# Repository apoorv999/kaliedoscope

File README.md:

# Kaliedoscope
This project is arduino based Kaliedoscope, developed at CEDT, NSUT. It comprises of two layers of boards. Top layer contains 4 RGB LEDs, switch, USB port for charging and connector for lipo battery. The  lower layer consists of Arduino nano, tilt sensors and power on LED. In this repository you can find the schematic and board files of these layers of boards and also the code for arduino (.ino) for this project.
## Images

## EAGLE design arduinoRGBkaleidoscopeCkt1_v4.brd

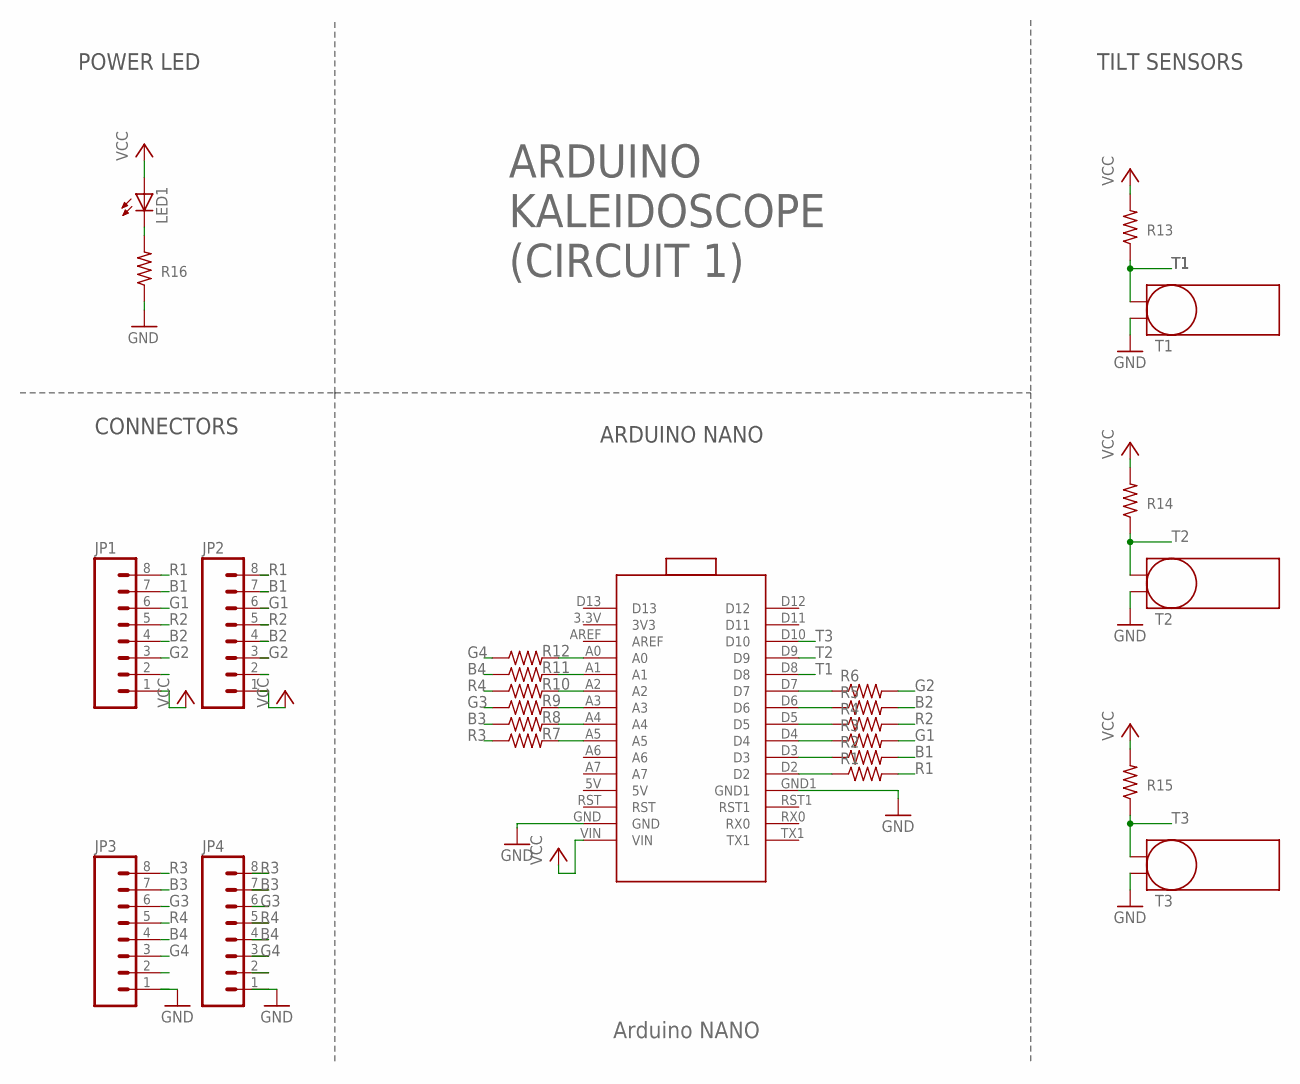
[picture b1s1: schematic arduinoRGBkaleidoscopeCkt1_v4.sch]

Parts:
JP1, JP2, JP3, JP4: M081X08; 1X08
LED1: LED3MM
R1, R2, R3, R4, R5, R6, R7, R8, R9, R10, R11, R12: RESISTOR0805; R0805
R13, R14, R15, R16: R-US_0204/7; 0204/7
T1, T2, T3: TILTSENSORE2.5-7; TILTSENSOR
U$2: NANO; NANO-2

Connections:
B1: JP1.7, JP2.7, R2.2
B2: JP1.4, JP2.4, R5.2
B3: JP3.7, JP4.7, R8.1
B4: JP3.4, JP4.4, R11.1
G1: JP1.6, JP2.6, R3.2
G2: JP1.3, JP2.3, R6.2
G3: JP3.6, JP4.6, R9.1
G4: JP3.3, JP4.3, R12.1
GND: JP3.1, JP4.1, R16.1, T1.-, T2.-, T3.-, U$2.GND, U$2.GND1
unnamed: R12.2, U$2.A0
unnamed: R11.2, U$2.A1
unnamed: R10.2, U$2.A2
unnamed: R9.2, U$2.A3
unnamed: R8.2, U$2.A4
unnamed: R7.2, U$2.A5
unnamed: R6.1, U$2.D7
unnamed: R5.1, U$2.D6
unnamed: R4.1, U$2.D5
unnamed: R3.1, U$2.D4
unnamed: R2.1, U$2.D3
unnamed: R1.1, U$2.D2
unnamed: LED1.K (C), R16.2
R1: JP1.8, JP2.8, R1.2
R2: JP1.5, JP2.5, R4.2
R3: JP3.8, JP4.8, R7.1
R4: JP3.5, JP4.5, R10.1
T1: R13.1, T1.+, U$2.D8
T2: R14.1, T2.+, U$2.D9
T3: R15.1, T3.+, U$2.D10
VCC: JP1.1, JP2.1, LED1.A, R13.2, R14.2, R15.2, U$2.VIN

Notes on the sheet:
Arduino NANO
POWER LED
TILT SENSORS
ARDUINO NANO
CONNECTORS
ARDUINO KALEIDOSCOPE (CIRCUIT 1)

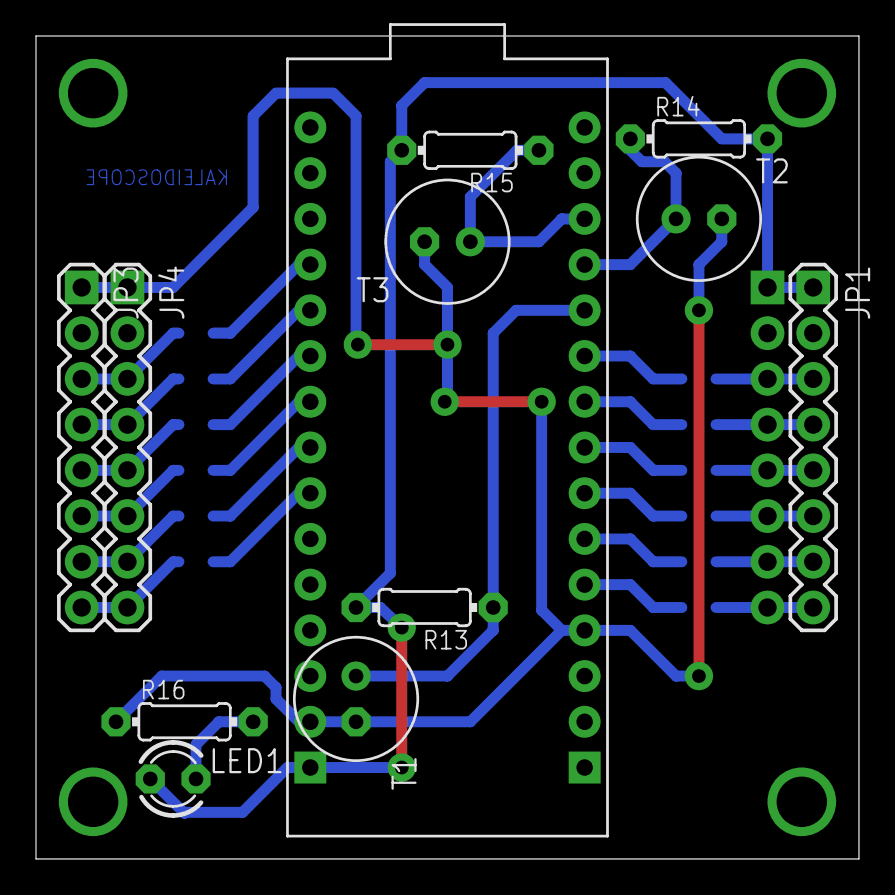
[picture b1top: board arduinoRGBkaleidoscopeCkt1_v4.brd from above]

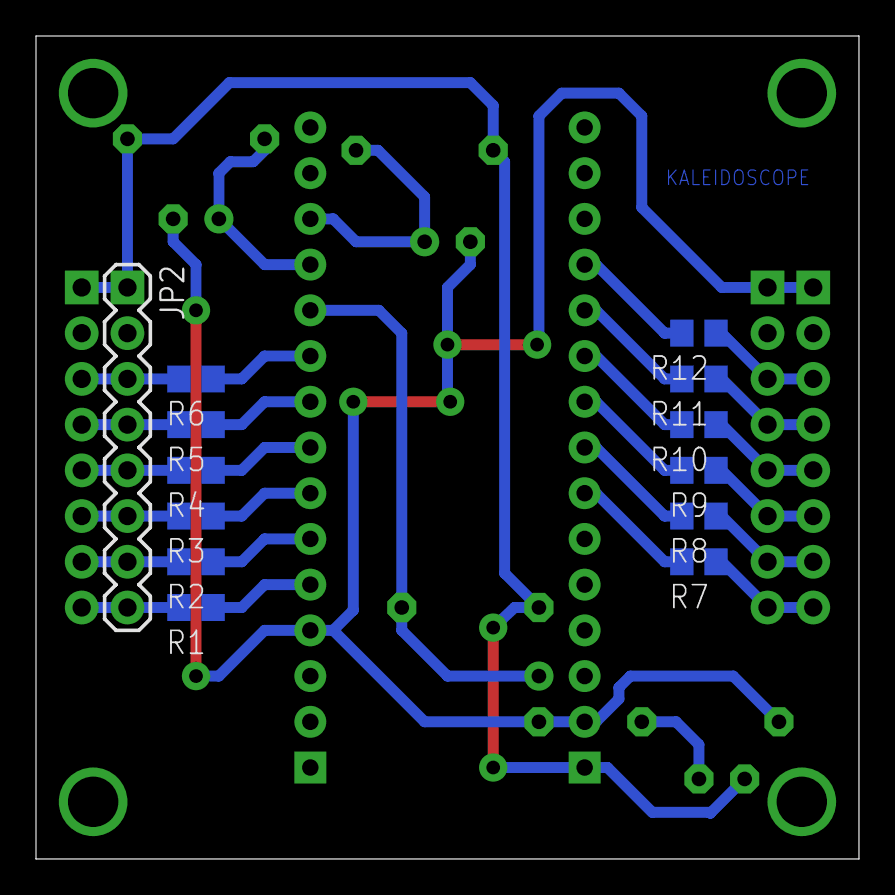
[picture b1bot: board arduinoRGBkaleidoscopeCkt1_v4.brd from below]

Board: 2 copper layers, 45.7 x 45.7 mm, 25 parts (13 on the bottom side), 30 nets.

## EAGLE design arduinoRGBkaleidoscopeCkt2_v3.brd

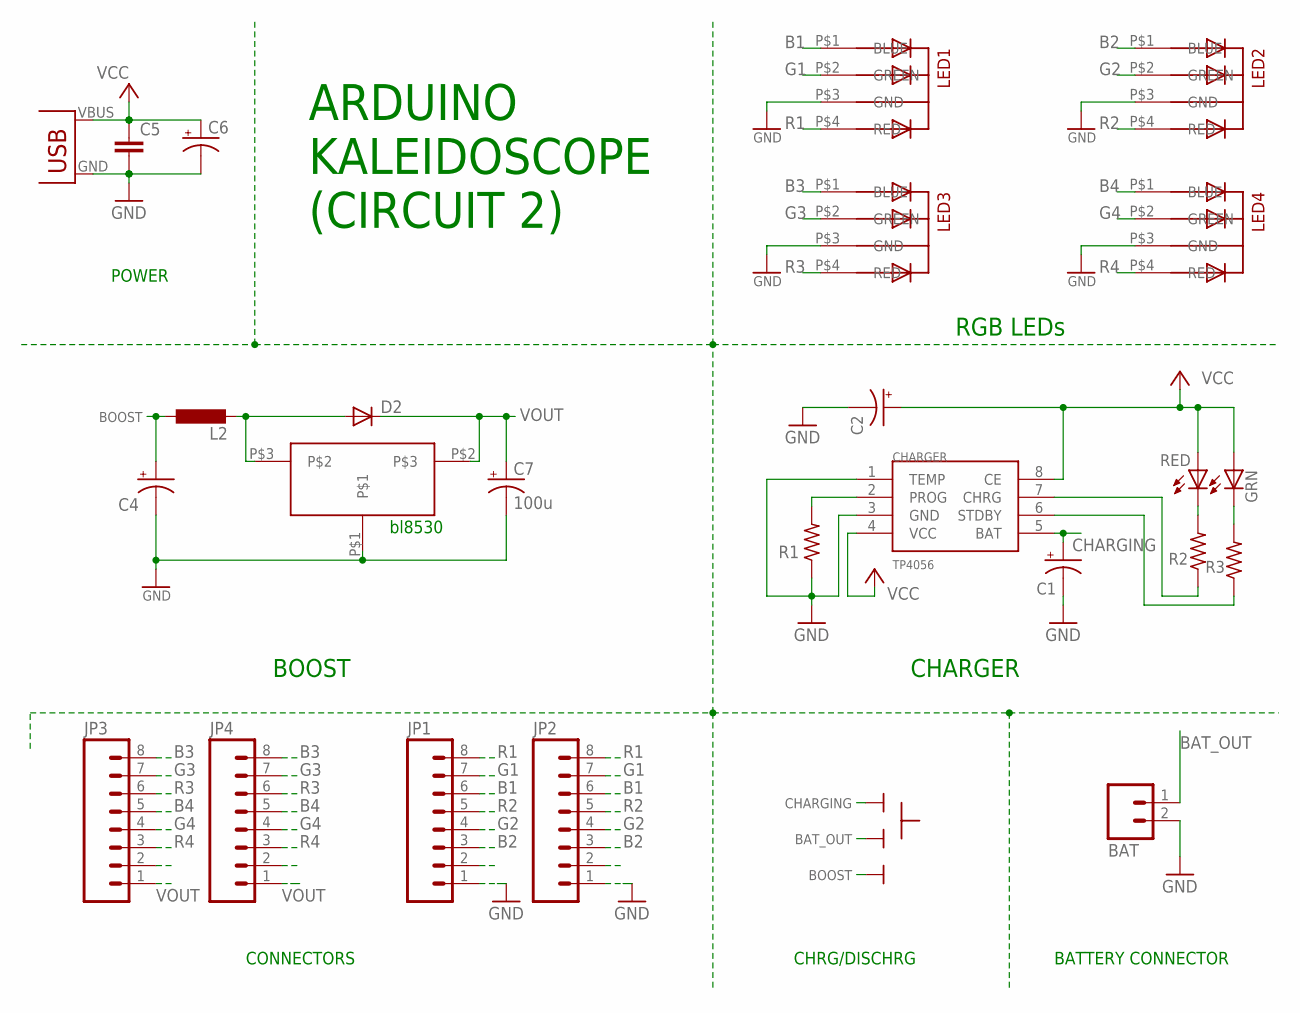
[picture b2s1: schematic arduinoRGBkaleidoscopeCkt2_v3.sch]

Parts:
BAT: M02; 02P
BOOST: BL8530_5V
C1, C2, C4: 10u; C/6032-28R
C5: C-EU025-024X044; C025-024X044
C6: CPOL-USE2,5-6E; E2,5-6E
C7: 100u; C/6032-28R
CHARGER: TP4056; SOP-8
CHRG/DISCHRG: SLIDESWITCH-BIG; BIGSWITCH
D2: DIODE-DO214AA; DO214AA
GRN: LED3MM; CHIPLED_0805
JP1, JP2, JP3, JP4: M081X08; 1X08
L2: 47uH; L4532P
LED1, LED2, LED3, LED4: 5MMRGBLED; LED5MMRGB
R1: RESISTOR0805; R0805
R2, R3: 470; R0805
RED: LED3MM; CHIPLED_0805
U$1: USB(POWER)

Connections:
B1: JP1.6, JP2.6, LED1.P$1 (BLUE)
B2: JP1.3, JP2.3, LED2.P$1 (BLUE)
B3: JP3.8, JP4.8, LED3.P$1 (BLUE)
B4: JP3.5, JP4.5, LED4.P$1 (BLUE)
BAT_OUT: BAT.1, CHRG/DISCHRG.2
BOOST: C4.+, CHRG/DISCHRG.3, L2.1
CHARGING: C1.+, CHARGER.5 (BAT), CHRG/DISCHRG.1
G1: JP1.7, JP2.7, LED1.P$2 (GREEN)
G2: JP1.4, JP2.4, LED2.P$2 (GREEN)
G3: JP3.7, JP4.7, LED3.P$2 (GREEN)
G4: JP3.4, JP4.4, LED4.P$2 (GREEN)
GND: BAT.2, BOOST.P$1, C1.-, C2.-, C4.-, C5.2, C6.-, C7.-, CHARGER.1 (TEMP), CHARGER.3 (GND), JP1.1, JP2.1, LED1.P$3 (GND), LED2.P$3 (GND), LED3.P$3 (GND), LED4.P$3 (GND), R1.1, U$1.GND
unnamed: CHARGER.2 (PROG), R1.2
unnamed: R2.2, RED.C
unnamed: CHARGER.7 (CHRG), R2.1
unnamed: CHARGER.6 (STDBY), R3.1
unnamed: BOOST.P$3, D2.A, L2.2
unnamed: GRN.C, R3.2
R1: JP1.8, JP2.8, LED1.P$4 (RED)
R2: JP1.5, JP2.5, LED2.P$4 (RED)
R3: JP3.6, JP4.6, LED3.P$4 (RED)
R4: JP3.3, JP4.3, LED4.P$4 (RED)
VCC: C2.+, C5.1, C6.+, CHARGER.4 (VCC), CHARGER.8 (CE), GRN.A, RED.A, U$1.VBUS (VCC)
VOUT: BOOST.P$2, C7.+, D2.C, JP3.1, JP4.1

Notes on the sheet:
BOOST
bl8530
CHARGER
RGB LEDs
POWER
BATTERY CONNECTOR
CONNECTORS
ARDUINO KALEIDOSCOPE (CIRCUIT 2)

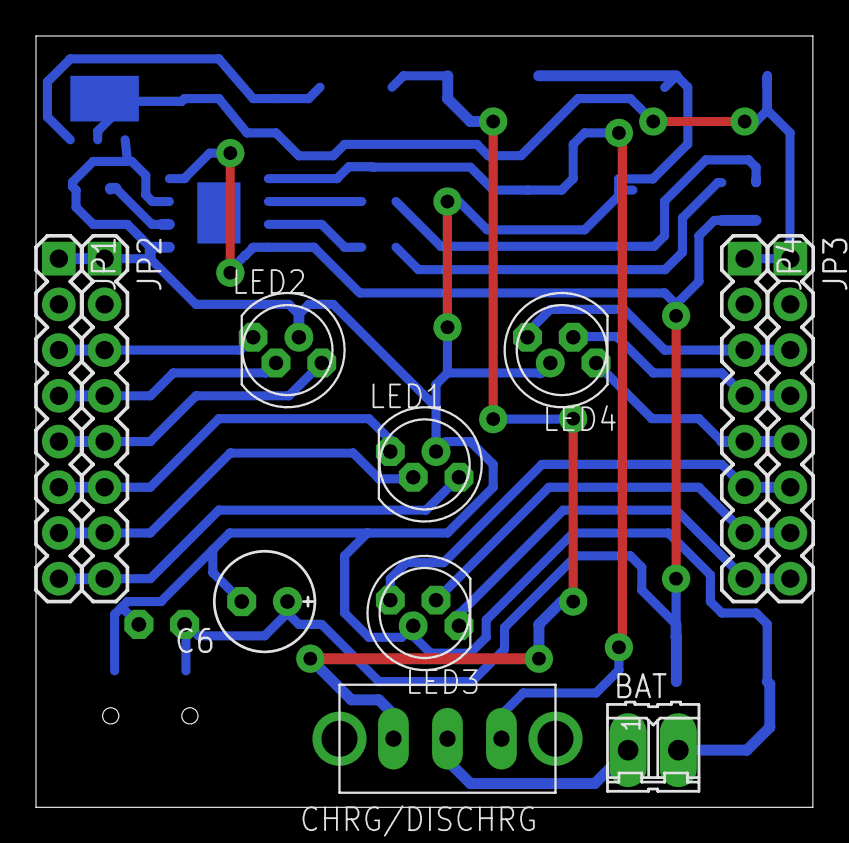
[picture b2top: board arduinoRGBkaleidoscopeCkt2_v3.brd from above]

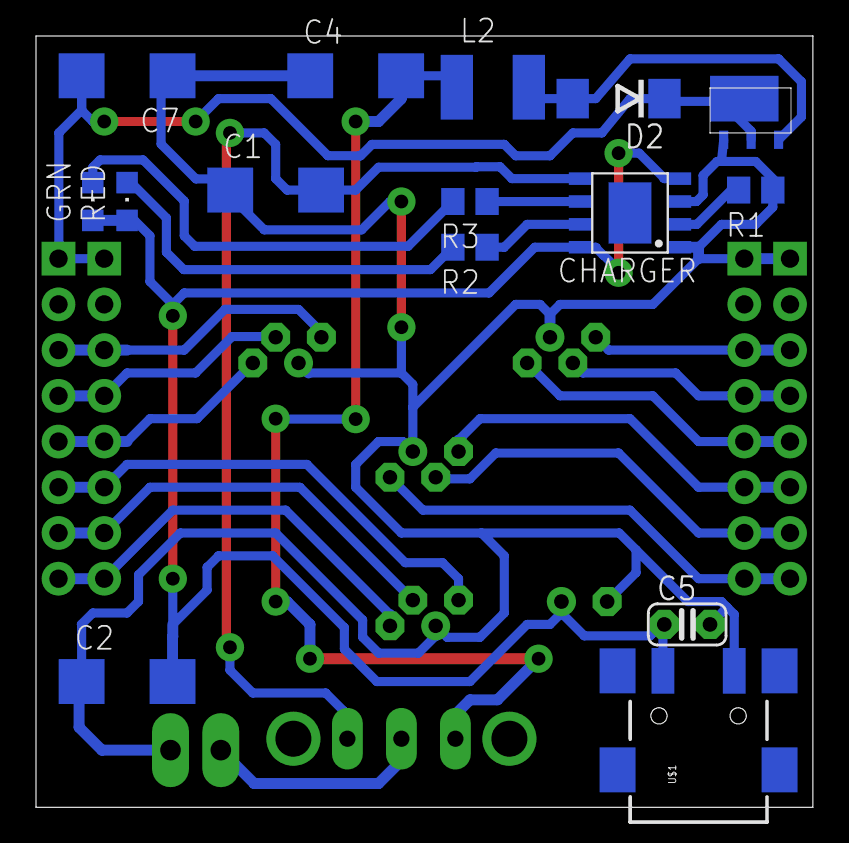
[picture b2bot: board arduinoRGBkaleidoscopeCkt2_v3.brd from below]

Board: 2 copper layers, 43.2 x 42.9 mm, 26 parts (15 on the bottom side), 24 nets.

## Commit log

2020-01-02 my first commit
2020-01-02 eagle files updated
2020-01-02 updated eagle files
2020-04-26 updated the README
2020-04-26 All files updated
2020-04-26 adding images
2020-04-26 Revert "adding images"
    This reverts commit 499a5489c1152090637c09b69f73e813fe83c0f6.
2020-04-26 Revert "Revert "adding images""
    This reverts commit 3ecb5ff8b754ffcbb9ecdc7be87cec5b7ba1a4a6.
2020-04-26 Revert "Revert "Revert "adding images"""
    This reverts commit 6c0f2568b4b2bce783b0f309465517bd66e400d8.
2020-04-26 Final Revert
    This reverts commit 31e28d348c4118bffbd8edc93a99dd4425131645.
2020-04-26 Images added to repo
2020-04-26 Deleted some images
2020-04-26 added gitignore
2020-04-26 ignore test file
2020-04-26 Added Images in README

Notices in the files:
parts and their libraries:
SparkFun-Connectors: Licensing: CC v3.0 Share-Alike You are welcome to use this library for commercial purposes.
